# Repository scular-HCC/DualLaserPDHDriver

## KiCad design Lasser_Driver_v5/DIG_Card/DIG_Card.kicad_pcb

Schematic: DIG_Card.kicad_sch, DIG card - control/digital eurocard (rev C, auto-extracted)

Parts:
A1: TEENSY_4.1; TEENSY_LONG_EXT
C80, C82, C84, C85: 100n; C_0805_2012Metric_Pad1.18x1.45mm_HandSolder
C81, C86: 100nF; C_0805_2012Metric_Pad1.18x1.45mm_HandSolder
C83, C87: 10n; C_0805_2012Metric_Pad1.18x1.45mm_HandSolder
C88, C92: 0.1uF; C_0805_2012Metric_Pad1.18x1.45mm_HandSolder
C89, C90, C91: 10nF; C_0805_2012Metric_Pad1.18x1.45mm_HandSolder
C301: 100nF U301 +15V; C_0805_2012Metric
C302: 100nF U301 -15V; C_0805_2012Metric
C303: 1n ERR1 ADC filter; C_0805_2012Metric
C304: 1n ERR2 ADC filter; C_0805_2012Metric
C305: 100nF U302 +15V; C_0805_2012Metric
C306: 100nF U302 -15V; C_0805_2012Metric
C307: 100nF U303 3V3; C_0805_2012Metric
C310: DNP MOD1 LPF; C_0805_2012Metric
C311: DNP MOD2 LPF; C_0805_2012Metric
C312: 100nF Y1 3V3_OSC; C_0805_2012Metric; MPN CL21B104KBCNNNC
C313: 1uF Y1 3V3_OSC; C_0805_2012Metric; MPN CC0805KKX7R8BB105
C314: 100nF U40 3V3; C_0805_2012Metric; MPN CL21B104KBCNNNC
C315: 100nF U41 3V3; C_0805_2012Metric; MPN CL21B104KBCNNNC
C316: 100nF U42 1V8; C_0805_2012Metric; MPN CL21B104KBCNNNC
C317: 100nF U42 3V3; C_0805_2012Metric; MPN CL21B104KBCNNNC
C318: 10uF U42 3V3; C_0805_2012Metric; MPN CC0805KKX5R7BB106
C319: 1uF U42 1V8_CLK; C_0805_2012Metric; MPN CC0805KKX7R8BB105
C320: 10nF U34 COMP; C_0805_2012Metric
C321: 10nF U39 COMP; C_0805_2012Metric
C322: 10uF +5V bulk; C_0805_2012Metric
C323: 10uF 3V3 bulk; C_0805_2012Metric
C324: 100nF 1V8 entry; C_0805_2012Metric
C325: 10uF 1V8 entry; C_0805_2012Metric
D24: BAV99; SOT-23
D301: BAT54S ERR1 ADC clamp; SOT-23
D302: BAT54S ERR2 ADC clamp; SOT-23
D303, D304, D305, D306, D307, D308, D309, D310, D311: BAT54WS VM fault OR; D_SOD-323
FB301: 600R@100MHz FB Y1; L_0805_2012Metric; MPN MPZ2012S601AT000
FB302: 600R@100MHz FB U42core; L_0805_2012Metric; MPN MPZ2012S601AT000
H1, H2: MountingHole; MountingHole_2.7mm
J2: 10MHz Ref SMA; SMA_BAT_Wireless_BWSMA-KWE-Z001
J301: DIN41612_M_universal; DIN41612_M_3x8+8_Male_Horizontal_THT_Power
J302: LO1 out SMA; SMA_BAT_Wireless_BWSMA-KWE-Z001
J302B1: Conn_Coaxial; SMA_BAT_Wireless_BWSMA-KWE-Z001
R104: 50; R_0805_2012Metric_Pad1.20x1.40mm_HandSolder
R105: 1M; R_0805_2012Metric_Pad1.20x1.40mm_HandSolder
R106: 27k; R_0805_2012Metric_Pad1.20x1.40mm_HandSolder
R107, R108, R111: 1k; R_0805_2012Metric_Pad1.20x1.40mm_HandSolder
R109: 100k; R_0805_2012Metric_Pad1.20x1.40mm_HandSolder
R110: 2M; R_0805_2012Metric_Pad1.20x1.40mm_HandSolder
R112, R113: 2.2k; R_0805_2012Metric_Pad1.20x1.40mm_HandSolder
R114: 100; R_0805_2012Metric_Pad1.20x1.40mm_HandSolder
R301, R302: 100R I2C series; R_0805_2012Metric
R303: 3k3 ERR1 ADC series; R_0805_2012Metric
R304: 3k3 ERR2 ADC series; R_0805_2012Metric
R305: 10k FAULT_n pullup; R_0805_2012Metric
R306: 47R MOD1 bus series; R_0805_2012Metric
R307: 47R MOD2 bus series; R_0805_2012Metric
R311: 33R CLK10M series; R_0805_2012Metric
R312: 49R9 LO1 series; R_0805_2012Metric
R313: 49R9 LO2 series; R_0805_2012Metric
R314: 0R MOD1 LPF (provision); R_0805_2012Metric
R315: 0R MOD2 LPF (provision); R_0805_2012Metric
R316: 33R MCLK2 series; R_0805_2012Metric
R317: 33R MCLK3 series; R_0805_2012Metric
TP301: N_U41_B1; TestPoint_Pad_D1.0mm
TP302: N_U41_A; TestPoint_Pad_D1.0mm
TP303: CLK10M_BUF; TestPoint_Pad_D1.0mm
TP304: MCLK1; TestPoint_Pad_D1.0mm
TP305: MCLK2; TestPoint_Pad_D1.0mm
TP306: 3V3_OSC; TestPoint_Pad_D1.0mm
TP307: 1V8_CLK; TestPoint_Pad_D1.0mm
TP308: 3V3; TestPoint_Pad_D1.0mm
TP309: +5V; TestPoint_Pad_D1.0mm
TP310: 1V8; TestPoint_Pad_D1.0mm
TP311: 5Vref; TestPoint_Pad_D1.0mm
TP312: VREF_MID; TestPoint_Pad_D1.0mm
TP313: VHI; TestPoint_Pad_D1.0mm
TP314: VLO; TestPoint_Pad_D1.0mm
TP315, TP316, TP317, TP318, TP319, TP320: GND; TestPoint_THTPad_D1.5mm_Drill0.7mm
U34, U39: AD9833xRM; MSOP-10_3x3mm_P0.5mm
U35, U38: AD9833xRM (ref); MSOP-10_3x3mm_P0.5mm
U40: LMV7219M5; SOT-23-5
U41: SN74LVC1G3157DBVR; SOT-23-6_Handsoldering
U42: CDCE913PWG4; SOP65P640X120-14N
U44: CR2013-MI2120
U301: OPA192IDBVR MOD1 buffer; SOT-23-5
U302: OPA192IDBVR MOD2 buffer; SOT-23-5
U303: 74LVC1G125 CLK10M bus buffer; SOT-23-5
VM_C75, VM_C76, VM_C77, VM_C78, VM_C79, VM_C80, VM_C90: 100nF; C_0805_2012Metric_Pad1.18x1.45mm_HandSolder
VM_C81, VM_C82, VM_C83, VM_C84, VM_C85, VM_C86, VM_C87, VM_C88, VM_C89: 10nF; C_0805_2012Metric_Pad1.18x1.45mm_HandSolder
VM_D16: +15V_OK; LED_0805_2012Metric_Pad1.15x1.40mm_HandSolder
VM_D17: -15V_OK; LED_0805_2012Metric_Pad1.15x1.40mm_HandSolder
VM_D18: +5V_OK; LED_0805_2012Metric_Pad1.15x1.40mm_HandSolder
VM_D19: -5V_OK; LED_0805_2012Metric_Pad1.15x1.40mm_HandSolder
VM_D20: +6V_OK; LED_0805_2012Metric_Pad1.15x1.40mm_HandSolder
VM_D21: -6V_OK; LED_0805_2012Metric_Pad1.15x1.40mm_HandSolder
VM_D22: +5VLaser_OK; LED_0805_2012Metric_Pad1.15x1.40mm_HandSolder
VM_D23: 3V3_OK; LED_0805_2012Metric_Pad1.15x1.40mm_HandSolder
VM_D24: 1V8_OK; LED_0805_2012Metric_Pad1.15x1.40mm_HandSolder
VM_Q11, VM_Q12, VM_Q13, VM_Q14, VM_Q15, VM_Q16, VM_Q17, VM_Q18, VM_Q19: MMBT3904; SOT-23
VM_R50: 29.4k; R_0805_2012Metric_Pad1.20x1.40mm_HandSolder
VM_R51: 1k; R_0805_2012Metric_Pad1.20x1.40mm_HandSolder
VM_R52: 9.53k; R_0805_2012Metric_Pad1.20x1.40mm_HandSolder
VM_R53: 110k; R_0805_2012Metric_Pad1.20x1.40mm_HandSolder
VM_R54, VM_R55, VM_R58, VM_R60, VM_R62, VM_R63, VM_R67, VM_R69, VM_R70, VM_R73, VM_R75, VM_R76, VM_R79, VM_R80, VM_R81, VM_R82, VM_R84, VM_R85, VM_R86, VM_R87: 10k; R_0805_2012Metric_Pad1.20x1.40mm_HandSolder
VM_R56, VM_R66, VM_R72: 100; R_0805_2012Metric_Pad1.20x1.40mm_HandSolder
VM_R59: 120k; R_0805_2012Metric_Pad1.20x1.40mm_HandSolder
VM_R61: 40.2k; R_0805_2012Metric_Pad1.20x1.40mm_HandSolder
VM_R64: 47.5k; R_0805_2012Metric_Pad1.20x1.40mm_HandSolder
VM_R65, VM_R77: 30.1k; R_0805_2012Metric_Pad1.20x1.40mm_HandSolder
VM_R71: 38.3k; R_0805_2012Metric_Pad1.20x1.40mm_HandSolder
VM_R78: 16.5k; R_0805_2012Metric_Pad1.20x1.40mm_HandSolder
VM_R83: 4.42k; R_0805_2012Metric_Pad1.20x1.40mm_HandSolder
VM_R88, VM_R89, VM_R90, VM_R91, VM_R92, VM_R93, VM_R94, VM_R95, VM_R96: 1.3k; R_0805_2012Metric_Pad1.20x1.40mm_HandSolder
VM_R97, VM_R98, VM_R99, VM_R100, VM_R101, VM_R102, VM_R103, VM_R104, VM_R105: 4.7k; R_0805_2012Metric_Pad1.20x1.40mm_HandSolder
VM_U22: MCP6002-xSN; SOIC-8_3.9x4.9mm_P1.27mm
VM_U23, VM_U25, VM_U26, VM_U27, VM_U28: LM339; SOIC-14_3.9x8.7mm_P1.27mm
VM_U24: MCP6004; SOIC-14_3.9x8.7mm_P1.27mm
Y1: ASE-10.000MHZ-LC-T; XTAL_ASE-10.000MHZ-LC-T

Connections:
1V8: C324.1, C325.1, FB302.2, J301.a19, R111.1, TP310.1 (1_1), VM_C81.2, VM_R83.1, VM_U28.9 (+), VM_U28.11 (+)
1V8_CLK: C316.1, C319.1, FB302.1, TP307.1 (1_1), U42.3 (VDD)
3.3V: A1.3V3 (3.3V), A1.3V3@2 (3.3V), A1.3V3@3 (3.3V)
3V3: C80.2, C84.2, C88.2, C92.2, C307.1, C314.1, C315.1, C317.1, C318.1, C323.1, D301.2 (K), D302.2 (K), FB301.1, J301.a18, R105.1, R112.2, R113.2, R114.2, R305.1, TP308.1 (1_1), U34.2 (VDD), U35.2 (VDD), U38.2 (VDD), U39.2 (VDD), U40.5 (V+), U41.5 (VCC), U42.6 (VDDOUT), U42.7 (VDDOUT), U44.1 (VCC), U303.5 (VCC), VM_R78.1
3V3_OSC: C312.1, C313.1, FB301.2, TP306.1 (1_1), Y1.1 (TRI-STATE(STBY)), Y1.4 (VDD)
5Vref: J301.b15, TP311.1 (1_1), VM_R50.1
+5V: A1.VIN, C322.1, J301.a16, TP309.1 (1_1), VM_C75.1, VM_C76.1, VM_C77.1, VM_C78.1, VM_C79.1, VM_C80.1, VM_C90.1, VM_R65.1, VM_R84.1, VM_R88.1, VM_R89.1, VM_R90.1, VM_R91.1, VM_R92.1, VM_R93.1, VM_R94.1, VM_R95.1, VM_R96.1, VM_R97.2, VM_R98.2, VM_R99.2, VM_R100.2, VM_R101.2, VM_R102.2, VM_R103.2, VM_R104.2, VM_R105.2, VM_U22.8 (V+), VM_U23.3 (V+), VM_U24.4 (V+), VM_U25.3 (V+), VM_U26.3 (V+), VM_U27.3 (V+), VM_U28.3 (V+)
+5V_LASER: J301.b13, VM_R77.1
+6V_TEC: J301.P1, VM_R71.1
+15V: C301.1, C305.1, J301.a13, U301.5 (V+), U302.5 (V+), VM_R53.1
+18V: J301.P5
-5V: J301.a17, VM_R61.1
-6V_TEC: J301.P3, VM_R64.1
-15V: C302.1, C306.1, J301.a14, U301.2 (V-), U302.2 (V-), VM_R59.1
-18V: J301.P7
/CLK10M_BUF: R311.1, TP303.1 (1_1), U303.4 (Y)
/DDS1_FSYNC: A1.D2, U34.8 (~FSYNC)
/DDS2_FSYNC: A1.D3, U39.8 (~FSYNC)
/DDS3_FSYNC: A1.D6, U35.8 (~FSYNC)
/DDS4_FSYNC: A1.D8, U38.8 (~FSYNC)
/ERR1_ADC: A1.D24 (A10), C303.1, D301.3 (COM), R303.2
/ERR2_ADC: A1.D25 (A11), C304.1, D302.3 (COM), R304.2
/LO1_OUT: J302.1 (In), R312.2
/LO2_OUT: J302B1.1 (In), R313.2
/MCLK1: TP304.1 (1_1), U34.5 (MCLK), U35.5 (MCLK), U42.11 (Y1)
/MCLK2: R316.2, TP305.1 (1_1), U38.5 (MCLK), U39.5 (MCLK)
/MCLK2_S: R316.1, U42.9 (Y2)
/MCLK3: A1.D9, R317.2
/MCLK3_S: R317.1, U42.8 (Y3)
/MOD1_BUF: R306.1, U301.1 (OUT), U301.4 (IN-)
/MOD1_IN: C310.1, R314.2, U301.3 (IN+)
/MOD2_BUF: R307.1, U302.1 (OUT), U302.4 (IN-)
/MOD2_IN: C311.1, R315.2, U302.3 (IN+)
/MOSI_3V3: A1.D11 ((SDO)D11), U34.6 (SDATA), U35.6 (SDATA), U38.6 (SDATA), U39.6 (SDATA)
/N_C89_Pad2: C89.2, R107.1
/N_C90_Pad2: C90.2, R108.1
/N_D24_A: C91.2, D24.2 (A), R109.1, R110.1, U40.3 (+)
/N_D24_K_Pad1: D24.1 (K), R108.2
/N_J2A_In1: C89.1, C90.1, J2.1 (In), R104.2
/N_U34_CAP/2_5V: C81.2, U34.3 (CAP/2.5V)
/N_U34_COMP: C320.1, U34.1 (COMP)
/N_U35_CAP/2_5V: C82.2, U35.3 (CAP/2.5V)
/N_U35_COMP: C83.1, U35.1 (COMP)
/N_U38_CAP/2_5V: C85.2, U38.3 (CAP/2.5V)
/N_U38_COMP: C87.1, U38.1 (COMP)
/N_U39_CAP/2_5V: C86.2, U39.3 (CAP/2.5V)
/N_U39_COMP: C321.1, U39.1 (COMP)
/N_U40__: R105.2, R106.1, U40.4 (-)
/N_U41_A: TP302.1 (1_1), U41.4 (A), U42.1 (XIN/CLK), U303.2 (A)
/N_U41_B1: TP301.1 (1_1), U41.3 (B1), Y1.3 (OUTPUT)
/N_U41_B2: R107.2, U41.1 (B2)
/N_U41_S: R110.2, U40.1, U41.6 (S)
/N_U42_S0: R111.2, U42.2 (S0)
/N_U44_D/~C: A1.D29, U44.5 (D/~C)
/N_U44_RESET: A1.D30, U44.4 (RESET)
/N_U44_~CS: A1.D28, U44.3 (~CS)
/OLD_AD5064_CLR: A1.D7
/OLD_CS_3V3: A1.D10 ((CS)D10)
/OLD_HBridgeFault2: A1.D32
/OLD_LAS2_IMON: A1.D22 (A8)
/OLD_LOCK1_EN: A1.D33
/OLD_LOCK2_EN: A1.D34
/OLD_MPD1_MON: A1.D17 (A3)
/OLD_MPD2_MON: A1.D23 (A9)
/OLD_NTC2_A: A1.D20 (A6)
/OLD_NTC_A14: A1.D38 (A14)
/OLD_TEC2_IMON: A1.D21 (A7)
/SCK_3V3: A1.D13 ((CLK)D13), U34.7 (SCLK), U35.7 (SCLK), U38.7 (SCLK), U39.7 (SCLK)
/TFT_MOSI: A1.D26 (A12), U44.6 (MOSI)
/TFT_SCK: A1.D27 (A13), U44.7 (SCK)
/VHI_Buf: TP313.1 (1_1), VM_U22.1, VM_U22.2 (-), VM_U23.5 (+), VM_U23.11 (+), VM_U25.5 (+), VM_U25.11 (+), VM_U26.5 (+), VM_U26.11 (+), VM_U27.5 (+), VM_U27.11 (+), VM_U28.5 (+)
/VLO_Buf: TP314.1 (1_1), VM_U22.6 (-), VM_U22.7, VM_U23.6 (-), VM_U23.8 (-), VM_U25.6 (-), VM_U25.8 (-), VM_U26.6 (-), VM_U26.8 (-), VM_U27.6 (-), VM_U27.8 (-), VM_U28.6 (-)
/VM_N_D16_A: VM_D16.2 (A), VM_R96.2
/VM_N_D16_K: VM_D16.1 (K), VM_Q11.3 (C)
/VM_N_D17_A: VM_D17.2 (A), VM_R95.2
/VM_N_D17_K: VM_D17.1 (K), VM_Q12.3 (C)
/VM_N_D18_A: VM_D18.2 (A), VM_R94.2
/VM_N_D18_K: VM_D18.1 (K), VM_Q13.3 (C)
/VM_N_D19_A: VM_D19.2 (A), VM_R93.2
/VM_N_D19_K: VM_D19.1 (K), VM_Q14.3 (C)
/VM_N_D20_A: VM_D20.2 (A), VM_R92.2
/VM_N_D20_K: VM_D20.1 (K), VM_Q15.3 (C)
/VM_N_D21_A: VM_D21.2 (A), VM_R91.2
/VM_N_D22_A: VM_D22.2 (A), VM_R88.2
/VM_N_D22_K: VM_D22.1 (K), VM_Q17.3 (C)
/VM_N_D23_K: VM_D23.1 (K), VM_Q18.3 (C)
/VM_N_D24_A: VM_D24.2 (A), VM_R90.2
/VM_N_D24_K: VM_D24.1 (K), VM_Q19.3 (C)
/VM_N_Q11_B: VM_Q11.1 (B), VM_R55.2
/VM_N_Q12_B: VM_Q12.1 (B), VM_R58.2
/VM_N_Q13_B: VM_Q13.1 (B), VM_R69.2
/VM_N_Q14_B: VM_Q14.1 (B), VM_R70.2
/VM_N_Q15_B: VM_Q15.1 (B), VM_R75.2
/VM_N_Q16_B: VM_Q16.1 (B), VM_R76.2
/VM_N_Q17_B: VM_Q17.1 (B), VM_R81.2
/VM_N_Q18_B: VM_Q18.1 (B), VM_R82.2
/VM_N_Q19_B: VM_Q19.1 (B), VM_R87.2
/VM_N_R55_Pad1: D303.1 (K), VM_R55.1, VM_R97.1, VM_U23.1, VM_U23.2
/VM_N_R56_Pad1: VM_R56.1, VM_R60.2, VM_U24.1
/VM_N_R58_Pad1: D304.1 (K), VM_R58.1, VM_R98.1, VM_U23.13, VM_U23.14
/VM_N_R62_Pad2: VM_R62.2, VM_R66.1, VM_U24.7
/VM_N_R63_Pad2: VM_R63.1, VM_R72.1, VM_U24.8
/VM_N_R69_Pad1: D305.1 (K), VM_R69.1, VM_R99.1, VM_U25.1, VM_U25.2
/VM_N_R100_Pad1: D306.1 (K), VM_R70.1, VM_R100.1, VM_U25.13, VM_U25.14
/VM_N_R101_Pad1: D307.1 (K), VM_R75.1, VM_R101.1, VM_U26.1, VM_U26.2
/VM_N_R102_Pad1: D308.1 (K), VM_R76.1, VM_R102.1, VM_U26.13, VM_U26.14
/VM_N_R103_Pad1: D309.1 (K), VM_R87.1, VM_R103.1, VM_U28.1, VM_U28.2
/VM_N_R104_Pad1: D310.1 (K), VM_R82.1, VM_R104.1, VM_U27.13, VM_U27.14
/VM_N_R105_Pad1: D311.1 (K), VM_R81.1, VM_R105.1, VM_U27.1, VM_U27.2
/VM_N_U23A__: VM_C84.1, VM_R53.2, VM_R54.1, VM_U23.4 (-), VM_U23.7 (+)
/VM_N_U23C__: VM_C85.1, VM_R56.2, VM_U23.9 (+), VM_U23.10 (-)
/VM_N_U24A__: VM_R59.2, VM_R60.1, VM_U24.2 (-)
/VM_N_U24B__: VM_R61.2, VM_R62.1, VM_U24.6 (-)
/VM_N_U24C__: VM_R63.2, VM_R64.2, VM_U24.9 (-)
/VM_N_U24D_P: VM_R84.2, VM_R86.1, VM_U24.12 (+)
/VM_N_U24D__: VM_U24.13 (-), VM_U24.14
/VM_N_U25A__: VM_C86.1, VM_R65.2, VM_R67.1, VM_U25.4 (-), VM_U25.7 (+)
/VM_N_U25C__: VM_C87.1, VM_R66.2, VM_U25.9 (+), VM_U25.10 (-)
/VM_N_U26A__: VM_C88.1, VM_R71.2, VM_R73.1, VM_U26.4 (-), VM_U26.7 (+)
/VM_N_U26C__: VM_C89.1, VM_R72.2, VM_U26.9 (+), VM_U26.10 (-)
/VM_N_U27A__: VM_C83.1, VM_R77.2, VM_R79.1, VM_U27.4 (-), VM_U27.7 (+)
/VM_N_U27C__: VM_C82.1, VM_R78.2, VM_R80.1, VM_U27.9 (+), VM_U27.10 (-)
/VM_N_U28A__: VM_C81.1, VM_R83.2, VM_R85.1, VM_U28.4 (-), VM_U28.7 (+)
/_VoltageMonitor_VHI: VM_R50.2, VM_R51.1, VM_U22.3 (+)
/_VoltageMonitor_VLO: VM_R51.2, VM_R52.1, VM_U22.5 (+)
ERR1_BUS: J301.c13, R303.1
ERR2_BUS: J301.c14, R304.1
FAULT_n: A1.D31, D303.2 (A), D304.2 (A), D305.2 (A), D306.2 (A), D307.2 (A), D308.2 (A), D309.2 (A), D310.2 (A), D311.2 (A), J301.b20, R305.2
GND: A1.AGND/GND (GND), A1.GND, A1.GND@2 (GND), C80.1, C81.1, C82.1, C83.2, C84.1, C85.1, C86.1, C87.2, C88.1, C91.1, C92.1, C301.2, C302.2, C303.2, C304.2, C305.2, C306.2, C307.2, C310.2, C311.2, C312.2, C313.2, C314.2, C315.2, C316.2, C317.2, C318.2, C319.2, C320.2, C321.2, C322.2, C323.2, C324.2, C325.2, D301.1 (A), D302.1 (A), J2.2 (Ext), J301.P6, J301.P8, J301.a15, J301.b14, J301.b17, J301.c15, J302.2 (Ext), J302B1.2 (Ext), R104.1, R106.2, R109.2, TP315.1 (1_1), TP316.1 (1_1), TP317.1 (1_1), TP318.1 (1_1), TP319.1 (1_1), TP320.1 (1_1), U34.4 (DGND), U34.9 (AGND), U35.4 (DGND), U35.9 (AGND), U38.4 (DGND), U38.9 (AGND), U39.4 (DGND), U39.9 (AGND), U40.2 (V-), U41.2 (GND), U42.5 (GND), U42.10 (GND), U44.2 (GND), U303.1 (~OE), U303.3 (GND), VM_C75.2, VM_C76.2, VM_C77.2, VM_C78.2, VM_C79.2, VM_C80.2, VM_C82.2, VM_C83.2, VM_C84.2, VM_C85.2, VM_C86.2, VM_C87.2, VM_C88.2, VM_C89.2, VM_C90.2, VM_Q11.2 (E), VM_Q12.2 (E), VM_Q13.2 (E), VM_Q14.2 (E), VM_Q15.2 (E), VM_Q16.2 (E), VM_Q17.2 (E), VM_Q18.2 (E), VM_Q19.2 (E), VM_R52.2, VM_R54.2, VM_R67.2, VM_R73.2, VM_R79.2, VM_R80.2, VM_R85.2, VM_R86.2, VM_U22.4 (V-), VM_U23.12 (V-), VM_U24.3 (+), VM_U24.5 (+), VM_U24.10 (+), VM_U24.11 (V-), VM_U25.12 (V-), VM_U26.12 (V-), VM_U27.12 (V-), VM_U28.8 (-), VM_U28.10 (-), VM_U28.12 (V-), Y1.2 (GND/CASE)
LO1_REF: R312.1, U35.10 (VOUT)
LO2_REF: R313.1, U38.10 (VOUT)
MOD1_BUS: J301.c16, R306.2
MOD1_FILT: R314.1, U34.10 (VOUT)
MOD2_BUS: J301.c17, R307.2
MOD2_FILT: R315.1, U39.10 (VOUT)
unnamed: R114.1, U44.8 (LED)
unnamed: VM_D21.1 (K), VM_Q16.3 (C)
unnamed: VM_D23.2 (A), VM_R89.2
PGND_TEC: J301.P2, J301.P4
SCL: A1.D19 (A5), R113.1, R302.2, U42.12 (S2/SCL)
SCL_BUS: J301.b19, R302.1
SDA: A1.D18 (A4), R112.1, R301.2, U42.13 (S1/SDA)
SDA_BUS: J301.b18, R301.1
SPARE_CLK10M: J301.c20, R311.2
VREF_MID: J301.b16, TP312.1 (1_1)

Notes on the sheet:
I2C: Teensy = master; MCU_SDA/SCL merged onto card net SDA/SCL (also serves CDCE913); bus pullups = existing R112/R113 4.7k (Clock sheet) - the ONLY pullups on the whole backplane bus.
VoltageMonitor windows +/-15V, +/-5V, +/-6V_TEC, +5V_LASER, 3V3, 1V8. +/-18V blades (P5-P8) pass through UNMONITORED.
OLD_* nets = Teensy pins freed by the I2C migration (monitors, LOCK_EN, faults, CS/CLR, PowerNTC) - reassign in firmware pass.
I2C pullups R112/R113 4.7k -> 2.2k (sole pullups for 8-slot bus); VM fault nodes diode-ORed onto FAULT_n (D303-D311,
Wiring by net label at every pin (no graphic wires). AD5064 U37 REMOVED - setpoints now on-card I2C DACs (CH cards).
DDS MOD-LO GEN (v3, no AD5064)
is this clock buffer needed?
LO SMAs get 49R9 back-termination (R312/R313); MOD LPF provision R314/R315 0R + C310/C311 DNP ahead of buffers.
LO1/LO2 out via J302 front SMAs (coax to AFE card). 10MHz ref on Clock J2 as in v3.
BAT54WS, node LOW = rail fault pulls bus); 10MHz mux output buffered to bus c20 (U303 74LVC1G125 + R311 33R);
ASSEMBLY: CUT the VUSB-VIN pad on the Teensy 4.1 - otherwise plugging USB drives 5V onto the crate +5V rail.
CARD ADDRESS via on-card jumpers JP301-JP303 (10k pullups R308-R310 to 3V3): fit jumper = 0, open = 1.
Backplane GA pins a20/c18/c19 (GA*_BP) intentionally unused - address lives on the card (scheme change 2026-07-16).
GA0/GA1/GA2 = Teensy pins 14/15/16 (freed A0/A1/A2); FAULT_n = Teensy pin 31 (was HBridgeFault1) - matches firmware config.h.
TEENSY + TFT (v3)
ERR1/ERR2_BUS -> 3k3/1n RC + BAT54S clamp -> Teensy ADC (ERRn_ADC). Restores v3 R118/C98 dropped in the port.
REV C cleanups: U36 74AHCT125 deleted (fed removed AD5064); R3/R4/C3 PowerNTC divider deleted (A1.D38 -> OLD_NTC_A14);
REV C (2026-07-19): U301/U302 now real SOT-23-5 OPA192 symbol (v3 LT1028_2 numbering matched no package);
Teensy VIN moved 3V3 -> +5V (a16); ERR bus conditioned: 3k3 (R303/R304) + 1n (C303/C304) + BAT54S clamps (D301/D302).
DIG CARD rev C - v3 Teensy/laser_control/Clock + VoltageMonitor (power board, refs VM_*) + universal bus IF.
MOD buses buffered: DDS out (MODn_FILT) -> U301/U302 OPA192 follower -> 47R -> MODn_BUS.
BUS INTERFACE (new)

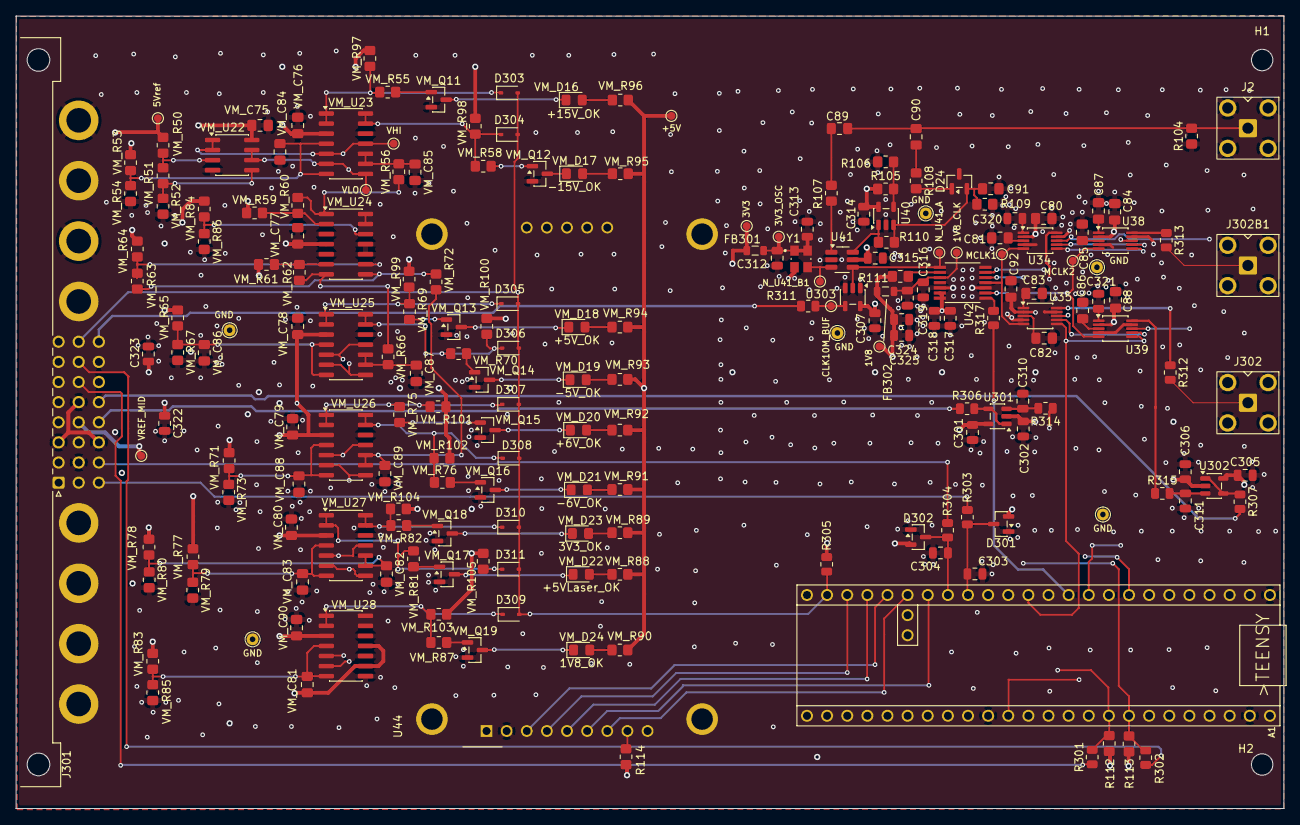
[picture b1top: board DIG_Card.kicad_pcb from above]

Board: 6 copper layers, 160.0 x 100.0 mm, 208 parts (1 on the bottom side), 132 nets.

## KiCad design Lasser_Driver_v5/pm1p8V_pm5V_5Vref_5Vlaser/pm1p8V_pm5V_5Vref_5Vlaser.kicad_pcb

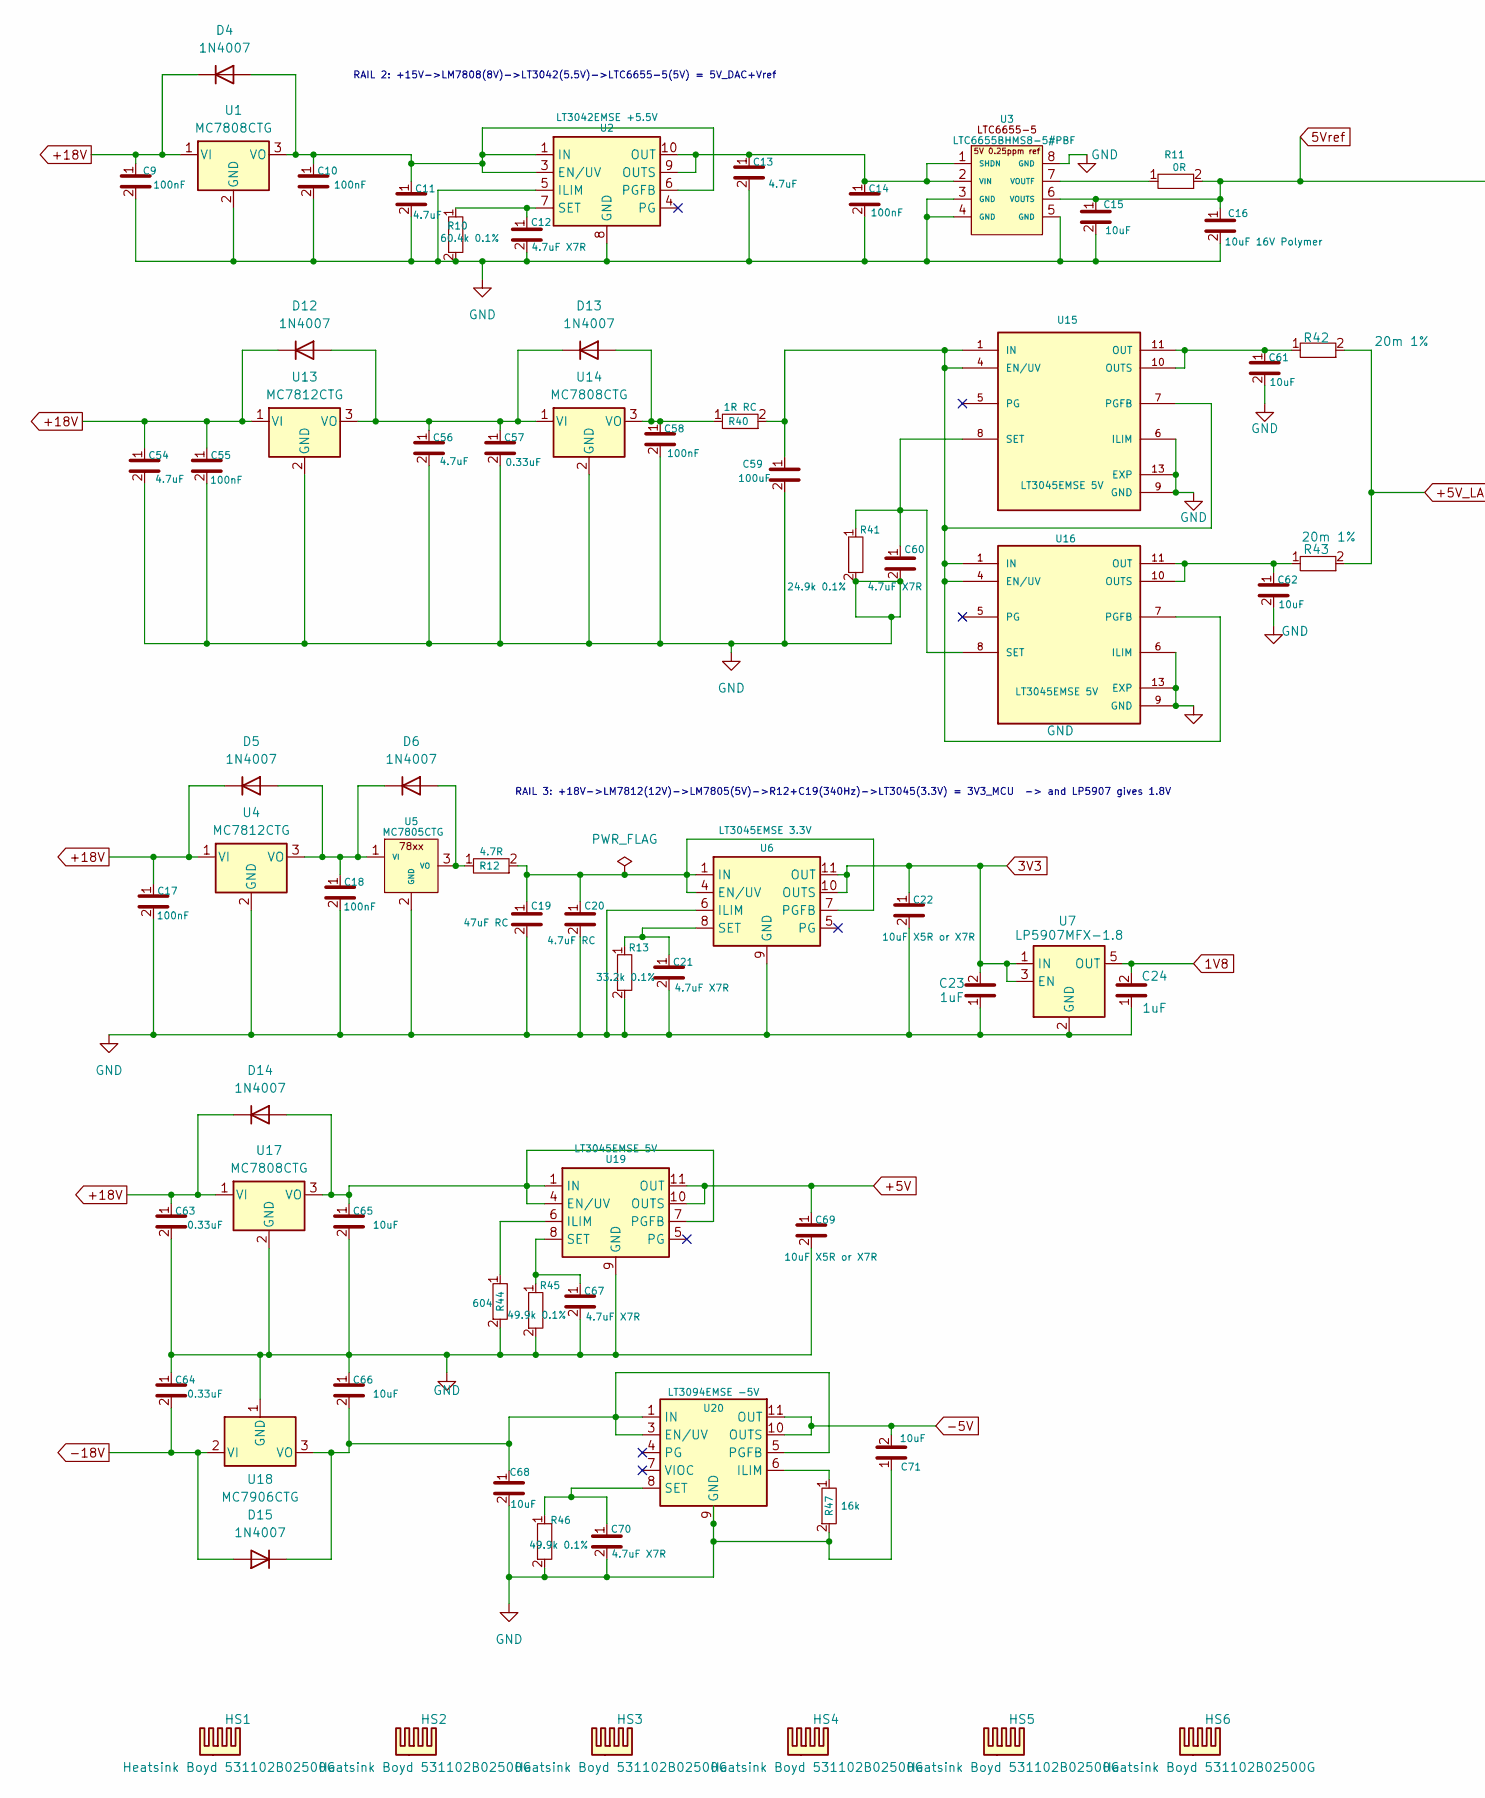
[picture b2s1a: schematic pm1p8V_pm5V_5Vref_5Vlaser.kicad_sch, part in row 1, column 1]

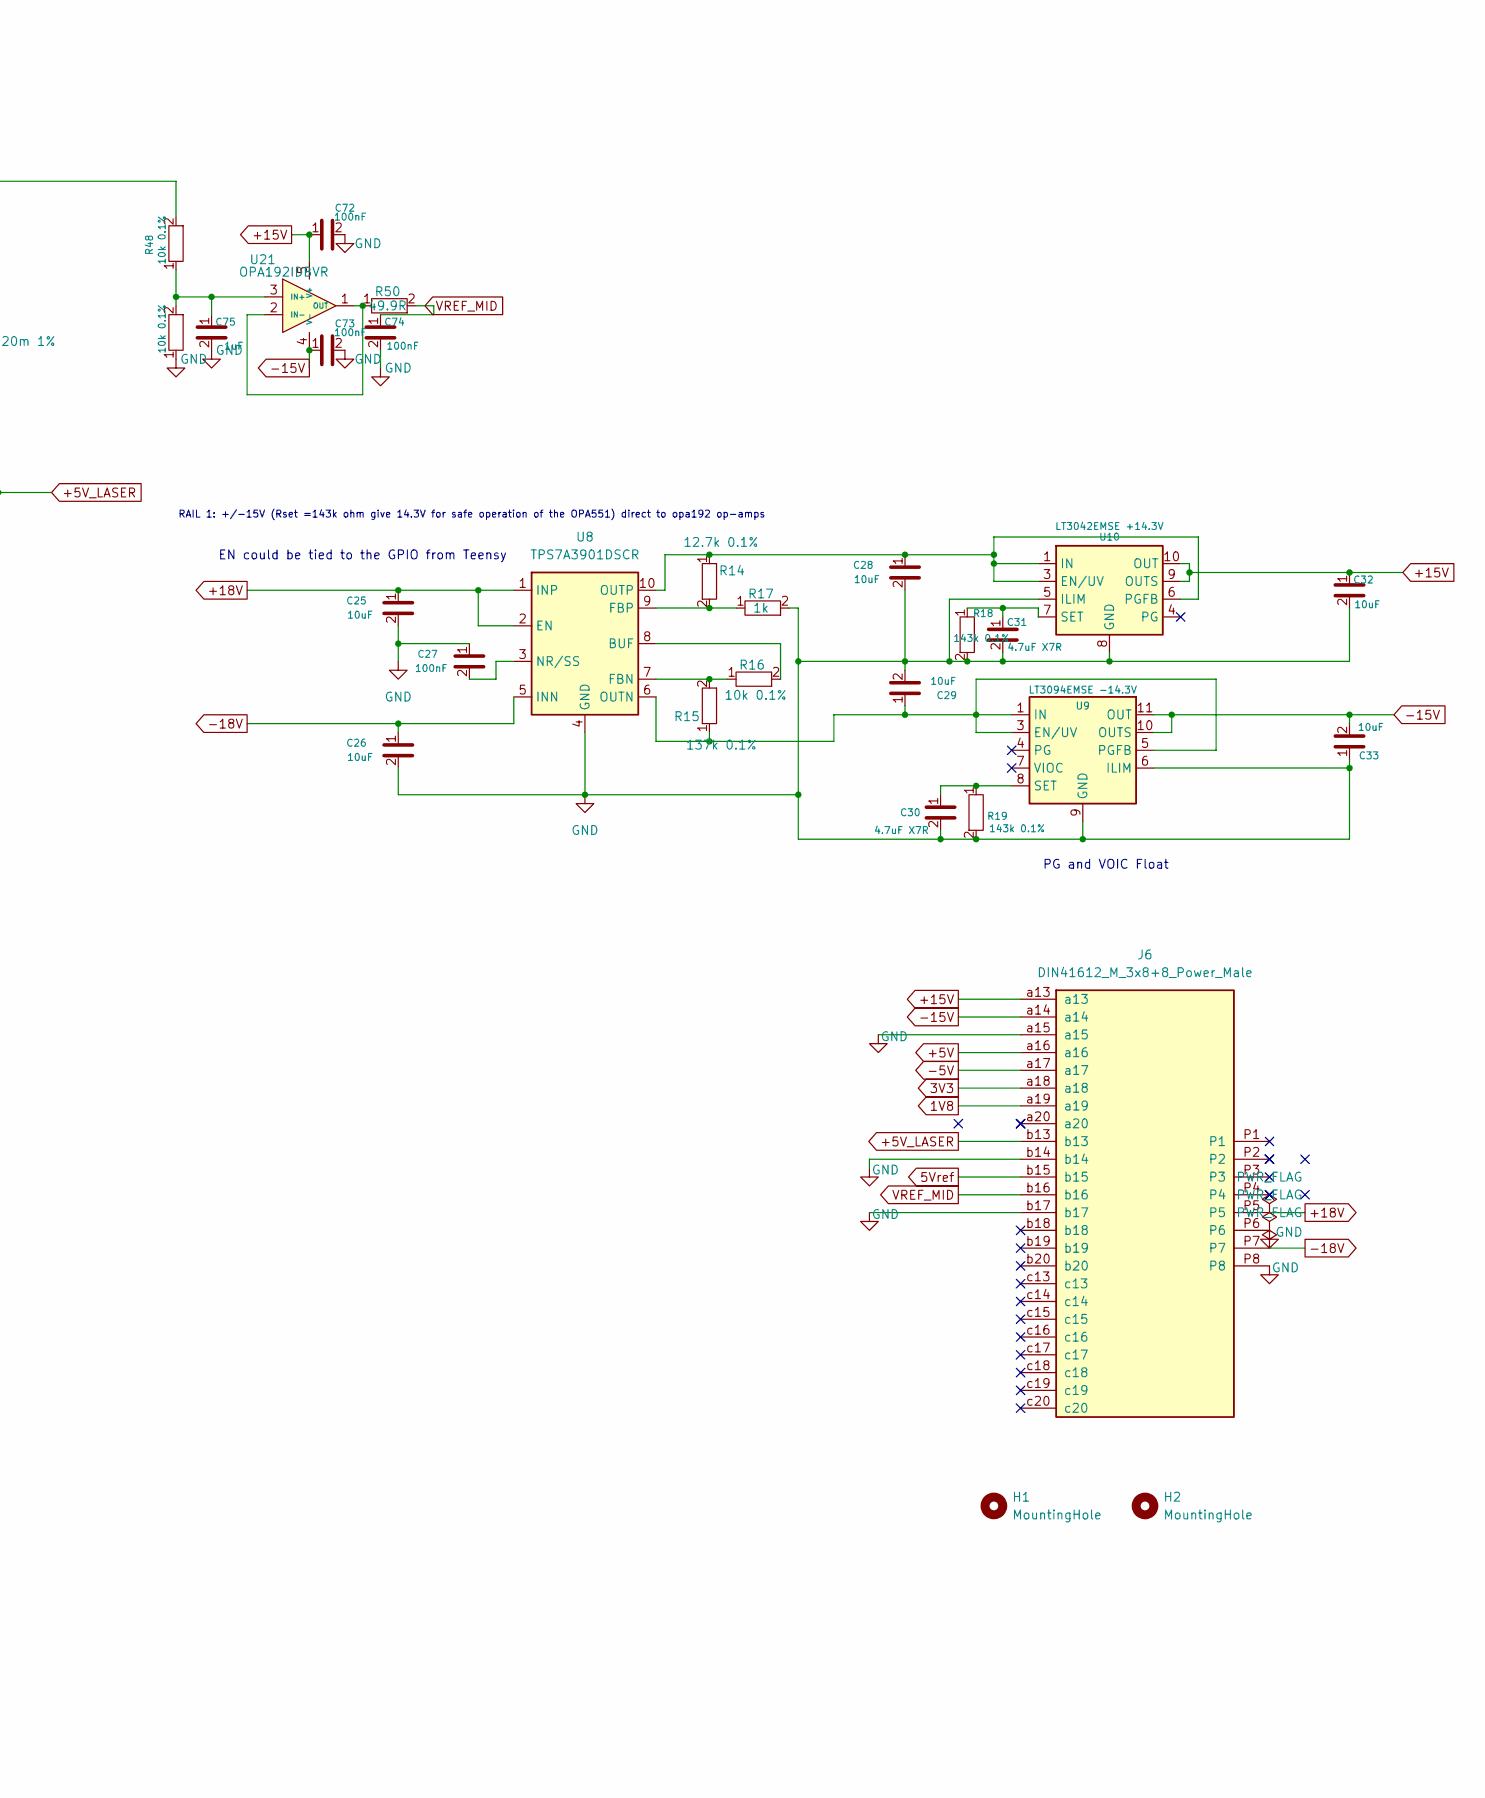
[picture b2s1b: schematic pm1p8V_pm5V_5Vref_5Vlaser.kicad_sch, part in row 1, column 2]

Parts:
C9, C10, C14, C17, C18, C27, C55, C58, C72, C73, C74: 100nF; C_0805_2012Metric_Pad1.18x1.45mm_HandSolder; Manufacturer Part Number CL21B104KBCNNNC; DigiKey P/N 1276-1003-2-ND
C11, C13, C54, C56: 4.7uF; C_0805_2012Metric_Pad1.18x1.45mm_HandSolder; Manufacturer Part Number CL21B475KAFNNNE; DigiKey P/N 1276-2969-2-ND
C12, C21, C30, C31, C60, C67, C70: 4.7uF X7R; C_0805_2012Metric_Pad1.18x1.45mm_HandSolder; Manufacturer Part Number CL21B475KAFNNNE; DigiKey P/N 1276-2969-2-ND
C15, C25, C26, C28, C29, C32, C33, C61, C62, C65, C66, C68, C71: 10uF; C_0805_2012Metric_Pad1.18x1.45mm_HandSolder; Manufacturer Part Number C0805C106K3PACTU; DigiKey P/N 399-11939-2-ND
C16: 10uF 16V Polymer; CP_EIA-3528-21_Kemet-B_HandSolder; Manufacturer Part Number T520B106M016ATE100; DigiKey P/N 399-5483-2-ND
C19: 47uF RC; C_1210_3225Metric_Pad1.33x2.70mm_HandSolder; Manufacturer Part Number TMK325ABJ476MM-P; DigiKey P/N 587-5479-2-ND
C20: 4.7uF RC; C_0805_2012Metric_Pad1.18x1.45mm_HandSolder; Manufacturer Part Number CL21B475KAFNNNE; DigiKey P/N 1276-2969-2-ND
C22, C69: 10uF X5R or X7R; C_0805_2012Metric_Pad1.18x1.45mm_HandSolder; Manufacturer Part Number C0805C106K3PACTU; DigiKey P/N 399-11939-2-ND
C23, C24: 1uF; C_0805_2012Metric_Pad1.18x1.45mm_HandSolder; Manufacturer Part Number C0805C105K5RACTU; DigiKey P/N 399-C0805C105K5RACTUTR-ND
C57, C63, C64: 0.33uF; C_0805_2012Metric_Pad1.18x1.45mm_HandSolder; Manufacturer Part Number CL21B334KBFNNNE; DigiKey P/N 1276-1123-2-ND
C59: 100uF; C_1210_3225Metric_Pad1.33x2.70mm_HandSolder; Manufacturer Part Number 1210YD107MAT2A; DigiKey P/N 478-11408-2-ND
C75: 1uF; C_0805_2012Metric_Pad1.18x1.45mm_HandSolder; Manufacturer Part Number C0805C105K5RACTU; DigiKey P/N 399-C0805C105K5RACTU-ND
D4, D5, D6, D12, D13, D14, D15: 1N4007; D_DO-41_SOD81_P12.70mm_Horizontal; Manufacturer Part Number 1N4007RLG; DigiKey P/N 1N4007RLGOSTR-ND
H1, H2: MountingHole; MountingHole_2.7mm
HS1, HS2, HS3, HS4, HS5, HS6: Heatsink Boyd 531102B02500G; Heatsink_AAVID_Extruded_531102B02500G_34.9x12.7mm_H38.1mm; Manufacturer Part Number 531102B02500G; DigiKey P/N HS352-ND
J6: DIN41612_M_3x8+8_Power_Male; DIN41612_M_3x8+8_Male_Horizontal_THT_Power; Manufacturer Part Number 374144-E; DigiKey P/N 2684-374144-E-ND
R10: 60.4k 0.1%; R_0805_2012Metric_Pad1.20x1.40mm_HandSolder; Manufacturer Part Number ERA-6AEB6042V; DigiKey P/N P60.4KDATR-ND
R11: 0R; R_0805_2012Metric_Pad1.20x1.40mm_HandSolder; Manufacturer Part Number RC0805JR-070RL; DigiKey P/N 311-0.0ARTR-ND
R12: 4.7R; R_1206_3216Metric_Pad1.30x1.75mm_HandSolder; Manufacturer Part Number RC1206FR-074R7L; DigiKey P/N 311-4.70FRTR-ND
R13: 33.2k 0.1%; R_0805_2012Metric_Pad1.20x1.40mm_HandSolder; Manufacturer Part Number ERA-6AEB3322V; DigiKey P/N P33.2KDATR-ND
R14: 12.7k 0.1%; R_0805_2012Metric_Pad1.20x1.40mm_HandSolder; Manufacturer Part Number ERA-6AEB1272V; DigiKey P/N P12.7KDATR-ND
R15: 137k 0.1%; R_0805_2012Metric_Pad1.20x1.40mm_HandSolder; Manufacturer Part Number ERA-6AEB1373V; DigiKey P/N 10-ERA-6AEB1373VTR-ND
R16, R48, R49: 10k 0.1%; R_0805_2012Metric_Pad1.20x1.40mm_HandSolder; Manufacturer Part Number ERA-6AEB103V; DigiKey P/N P10KDATR-ND
R17: 1k; R_0805_2012Metric_Pad1.20x1.40mm_HandSolder; Manufacturer Part Number CRCW08051K00FKEA; DigiKey P/N 541-1.00KCTR-ND
R18, R19: 143k 0.1%; R_0805_2012Metric_Pad1.20x1.40mm_HandSolder; Manufacturer Part Number ERA-6AEB1433V; DigiKey P/N P143KDATR-ND
R40: 1R RC; R_1206_3216Metric_Pad1.30x1.75mm_HandSolder; Manufacturer Part Number RC1206FR-071RL; DigiKey P/N 311-1.00FRTR-ND
R41: 24.9k 0.1%; R_0805_2012Metric_Pad1.20x1.40mm_HandSolder; Manufacturer Part Number ERA-6AEB2492V; DigiKey P/N P24.9KDATR-ND
R42, R43: 20m 1%; R_0805_2012Metric_Pad1.20x1.40mm_HandSolder; Manufacturer Part Number ERJ-6BWFR020V; DigiKey P/N P.02AQTR-ND
R44: 604; R_0805_2012Metric_Pad1.20x1.40mm_HandSolder; Manufacturer Part Number RC0805FR-07604RL; DigiKey P/N 311-604CRTR-ND
R45, R46: 49.9k 0.1%; R_0805_2012Metric_Pad1.20x1.40mm_HandSolder; Manufacturer Part Number ERA-6AEB4992V; DigiKey P/N P49.9KDATR-ND
R47: 16k; R_0805_2012Metric_Pad1.20x1.40mm_HandSolder; Manufacturer Part Number RC0805FR-0716KL; DigiKey P/N 311-16.0KCRTR-ND
R50: 49.9R; R_0805_2012Metric_Pad1.20x1.40mm_HandSolder; Manufacturer Part Number ERJ-6ENF49R9V; DigiKey P/N P49.9CTR-ND
U1, U14, U17: MC7808CTG; TO-220-3_Vertical; Manufacturer Part Number MC7808CTG; DigiKey P/N MC7808CTGOS-ND
U2: LT3042EMSE +5.5V; MSOP-10-1EP_3x3mm_P0.5mm_EP1.68x1.88mm; Manufacturer Part Number LT3042EMSE#PBF; DigiKey P/N 505-LT3042EMSE#PBF-ND
U3: LTC6655BHMS8-5#PBF; MSOP-8_3x3mm_P0.65mm; Manufacturer Part Number LTC6655BHMS8-5#PBF; DigiKey P/N 505-LTC6655BHMS8-5#PBF-ND
U4, U13: MC7812CTG; TO-220-3_Vertical; Manufacturer Part Number MC7812CTG; DigiKey P/N MC7812CTGOS-ND
U5: MC7805CTG; TO-220-3_Vertical; Manufacturer Part Number MC7805CTG; DigiKey P/N MC7805CTGOS-ND
U6: LT3045EMSE 3.3V; MSOP-12-1EP_3x4.039mm_P0.65mm_EP1.651x2.845mm; Manufacturer Part Number LT3045EMSE#PBF; DigiKey P/N 505-LT3045EMSE#PBF-ND
U7: LP5907MFX-1.8; SOT-23-5; Manufacturer Part Number LP5907MFX-1.8/NOPB; DigiKey P/N 296-41463-2-ND
U8: TPS7A3901DSCR; Texas_DSC0010J_ThermalVias; Manufacturer Part Number TPS7A3901DSCR; DigiKey P/N 296-TPS7A3901DSCRTR-ND
U9: LT3094EMSE -14.3V; MSOP-12-1EP_3x4.039mm_P0.65mm_EP1.651x2.845mm; Manufacturer Part Number LT3094EMSE#PBF; DigiKey P/N 505-LT3094EMSE#PBF-ND
U10: LT3042EMSE +14.3V; MSOP-10-1EP_3x3mm_P0.5mm_EP1.68x1.88mm; Manufacturer Part Number LT3042EMSE#PBF; DigiKey P/N 505-LT3042EMSE#PBF-ND
U15, U16: LT3045EMSE 5V; MSOP-12-1EP_3x4.039mm_P0.65mm_EP1.651x2.845mm_ThermalVias; PARTREV D; DigiKey P/N 505-LT3045EMSE#PBF-ND
U18: MC7906CTG; TO-220-3_Vertical; Manufacturer Part Number MC7906CTG; DigiKey P/N MC7906CTGOS-ND
U19: LT3045EMSE 5V; MSOP-12-1EP_3x4.039mm_P0.65mm_EP1.651x2.845mm; Manufacturer Part Number LT3045EMSE#PBF; DigiKey P/N 505-LT3045EMSE#PBF-ND
U20: LT3094EMSE -5V; MSOP-12-1EP_3x4.039mm_P0.65mm_EP1.651x2.845mm; Manufacturer Part Number LT3094EMSE#PBF; DigiKey P/N 505-LT3094EMSE#PBF-ND
U21: OPA192IDBVR; SOT-23-5_HandSoldering; Manufacturer Part Number OPA192IDBVR; DigiKey P/N 296-42105-2-ND

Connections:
1V8: C24.2, J6.a19, U7.5 (OUT)
3V3: C22.1, C23.2, J6.a18, U6.10 (OUTS), U6.11 (OUT), U6.12 (OUT), U7.1 (IN), U7.3 (EN)
5Vref: C15.1, C16.1, J6.b15, R11.2, R48.2, U3.6 (VOUTS)
+5V: C69.1, J6.a16, U19.10 (OUTS), U19.11 (OUT), U19.12 (OUT)
+5V_LASER: J6.b13, R42.2, R43.2
+15V: C32.1, C72.1, J6.a13, U10.9 (OUTS), U10.10 (OUT), U21.5 (V+)
+18V: C9.1, C17.1, C25.1, C54.1, C55.1, C63.1, D4.1 (K), D5.1 (K), D12.1 (K), D14.1 (K), J6.P5, U1.1 (VI), U4.1 (VI), U8.1 (INP), U8.2 (EN), U13.1 (VI), U17.1 (VI)
-5V: C71.2, J6.a17, U20.10 (OUTS), U20.11 (OUT), U20.12 (OUT)
-15V: C33.2, C73.1, J6.a14, U9.10 (OUTS), U9.11 (OUT), U9.12 (OUT), U21.4 (V-)
-18V: C26.1, C64.2, D15.2 (A), J6.P7, U8.5 (INN), U18.2 (VI)
GND: C9.2, C10.2, C11.2, C12.2, C13.2, C14.2, C15.2, C16.2, C17.2, C18.2, C19.2, C20.2, C21.2, C22.2, C23.1, C24.1, C25.2, C26.2, C27.1, C28.2, C29.2, C30.2, C31.2, C32.2, C33.1, C54.2, C55.2, C56.2, C57.2, C58.2, C59.2, C60.2, C61.2, C62.2, C63.2, C64.1, C65.2, C66.1, C67.2, C68.2, C69.2, C70.2, C71.1, C72.2, C73.2, C74.2, C75.2, J6.P6, J6.P8, J6.a15, J6.b14, J6.b17, R10.2, R13.2, R17.2, R18.2, R19.2, R41.2, R44.2, R45.2, R46.2, R47.2, R49.1, U1.2 (GND), U2.5 (ILIM), U2.8 (GND), U2.11 (GND), U3.3 (GND), U3.4 (GND), U3.5 (GND), U3.8 (GND), U4.2 (GND), U5.2 (GND), U6.6 (ILIM), U6.9 (GND), U6.13 (GND), U7.2 (GND), U8.4 (GND), U8.11 (GND), U9.6 (ILIM), U9.9 (GND), U10.5 (ILIM), U10.8 (GND), U10.11 (GND), U13.2 (GND), U14.2 (GND), U15.6 (ILIM), U15.9 (GND), U15.13 (EXP), U16.6 (ILIM), U16.9 (GND), U16.13 (EXP), U17.2 (GND), U18.1 (GND), U19.9 (GND), U19.13 (GND), U20.9 (GND)
unnamed: C10.1, C11.1, D4.2 (A), U1.3 (VO), U2.1 (IN), U2.2 (IN), U2.3 (EN/UV), U2.6 (PGFB)
unnamed: C18.1, D5.2 (A), D6.1 (K), U4.3 (VO), U5.1 (VI)
unnamed: D6.2 (A), R12.1, U5.3 (VO)
unnamed: C56.1, C57.1, D12.2 (A), D13.1 (K), U13.3 (VO), U14.1 (VI)
unnamed: C58.1, D13.2 (A), R40.1, U14.3 (VO)
unnamed: C65.1, D14.2 (A), U17.3 (VO), U19.1 (IN), U19.2 (IN), U19.3 (IN), U19.4 (EN/UV), U19.7 (PGFB)
unnamed: C66.2, C68.1, D15.1 (K), U18.3 (VO), U20.1 (IN), U20.2 (IN), U20.3 (EN/UV), U20.5 (PGFB), U20.13 (IN)
unnamed: C13.1, C14.1, U2.9 (OUTS), U2.10 (OUT), U3.1 (SHDN), U3.2 (VIN)
unnamed: C12.1, R10.1, U2.7 (SET)
unnamed: R11.1, U3.7 (VOUTF)
unnamed: C19.1, C20.1, R12.2, U6.1 (IN), U6.2 (IN), U6.3 (IN), U6.4 (EN/UV), U6.7 (PGFB)
unnamed: C21.1, R13.1, U6.8 (SET)
unnamed: R16.2, U8.8 (BUF)
unnamed: R15.2, R16.1, U8.7 (FBN)
unnamed: R14.2, R17.1, U8.9 (FBP)
unnamed: C27.2, U8.3 (NR/SS)
unnamed: C29.1, R15.1, U8.6 (OUTN), U9.1 (IN), U9.2 (IN), U9.3 (EN/UV), U9.5 (PGFB), U9.13 (IN)
unnamed: C30.1, R19.1, U9.8 (SET)
unnamed: C28.1, R14.1, U8.10 (OUTP), U10.1 (IN), U10.2 (IN), U10.3 (EN/UV), U10.6 (PGFB)
unnamed: C31.1, R18.1, U10.7 (SET)
unnamed: C59.1, R40.2, U15.1 (IN), U15.2 (IN), U15.3 (IN), U15.4 (EN/UV), U15.7 (PGFB), U16.1 (IN), U16.2 (IN), U16.3 (IN), U16.4 (EN/UV), U16.7 (PGFB)
unnamed: C61.1, R42.1, U15.10 (OUTS), U15.11 (OUT), U15.12 (OUT)
unnamed: C60.1, R41.1, U15.8 (SET), U16.8 (SET)
unnamed: C62.1, R43.1, U16.10 (OUTS), U16.11 (OUT), U16.12 (OUT)
unnamed: R44.1, U19.6 (ILIM)
unnamed: C67.1, R45.1, U19.8 (SET)
unnamed: R47.1, U20.6 (ILIM)
unnamed: C70.1, R46.1, U20.8 (SET)
unnamed: C75.1, R48.1, R49.2, U21.3 (IN+)
unnamed: R50.1, U21.1 (OUT), U21.2 (IN-)
VREF_MID: C74.1, J6.b16, R50.2

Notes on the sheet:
EN could be tied to the GPIO from Teensy
PG and VOIC Float
RAIL 3: +18V->LM7812(12V)->LM7805(5V)->R12+C19(340Hz)->LT3045(3.3V) = 3V3_MCU -> and LP5907 gives 1.8V
RAIL 1: +/-15V (Rset =143k ohm give 14.3V for safe operation of the OPA551) direct to opa192 op-amps
RAIL 2: +15V->LM7808(8V)->LT3042(5.5V)->LTC6655-5(5V) = 5V_DAC+Vref
